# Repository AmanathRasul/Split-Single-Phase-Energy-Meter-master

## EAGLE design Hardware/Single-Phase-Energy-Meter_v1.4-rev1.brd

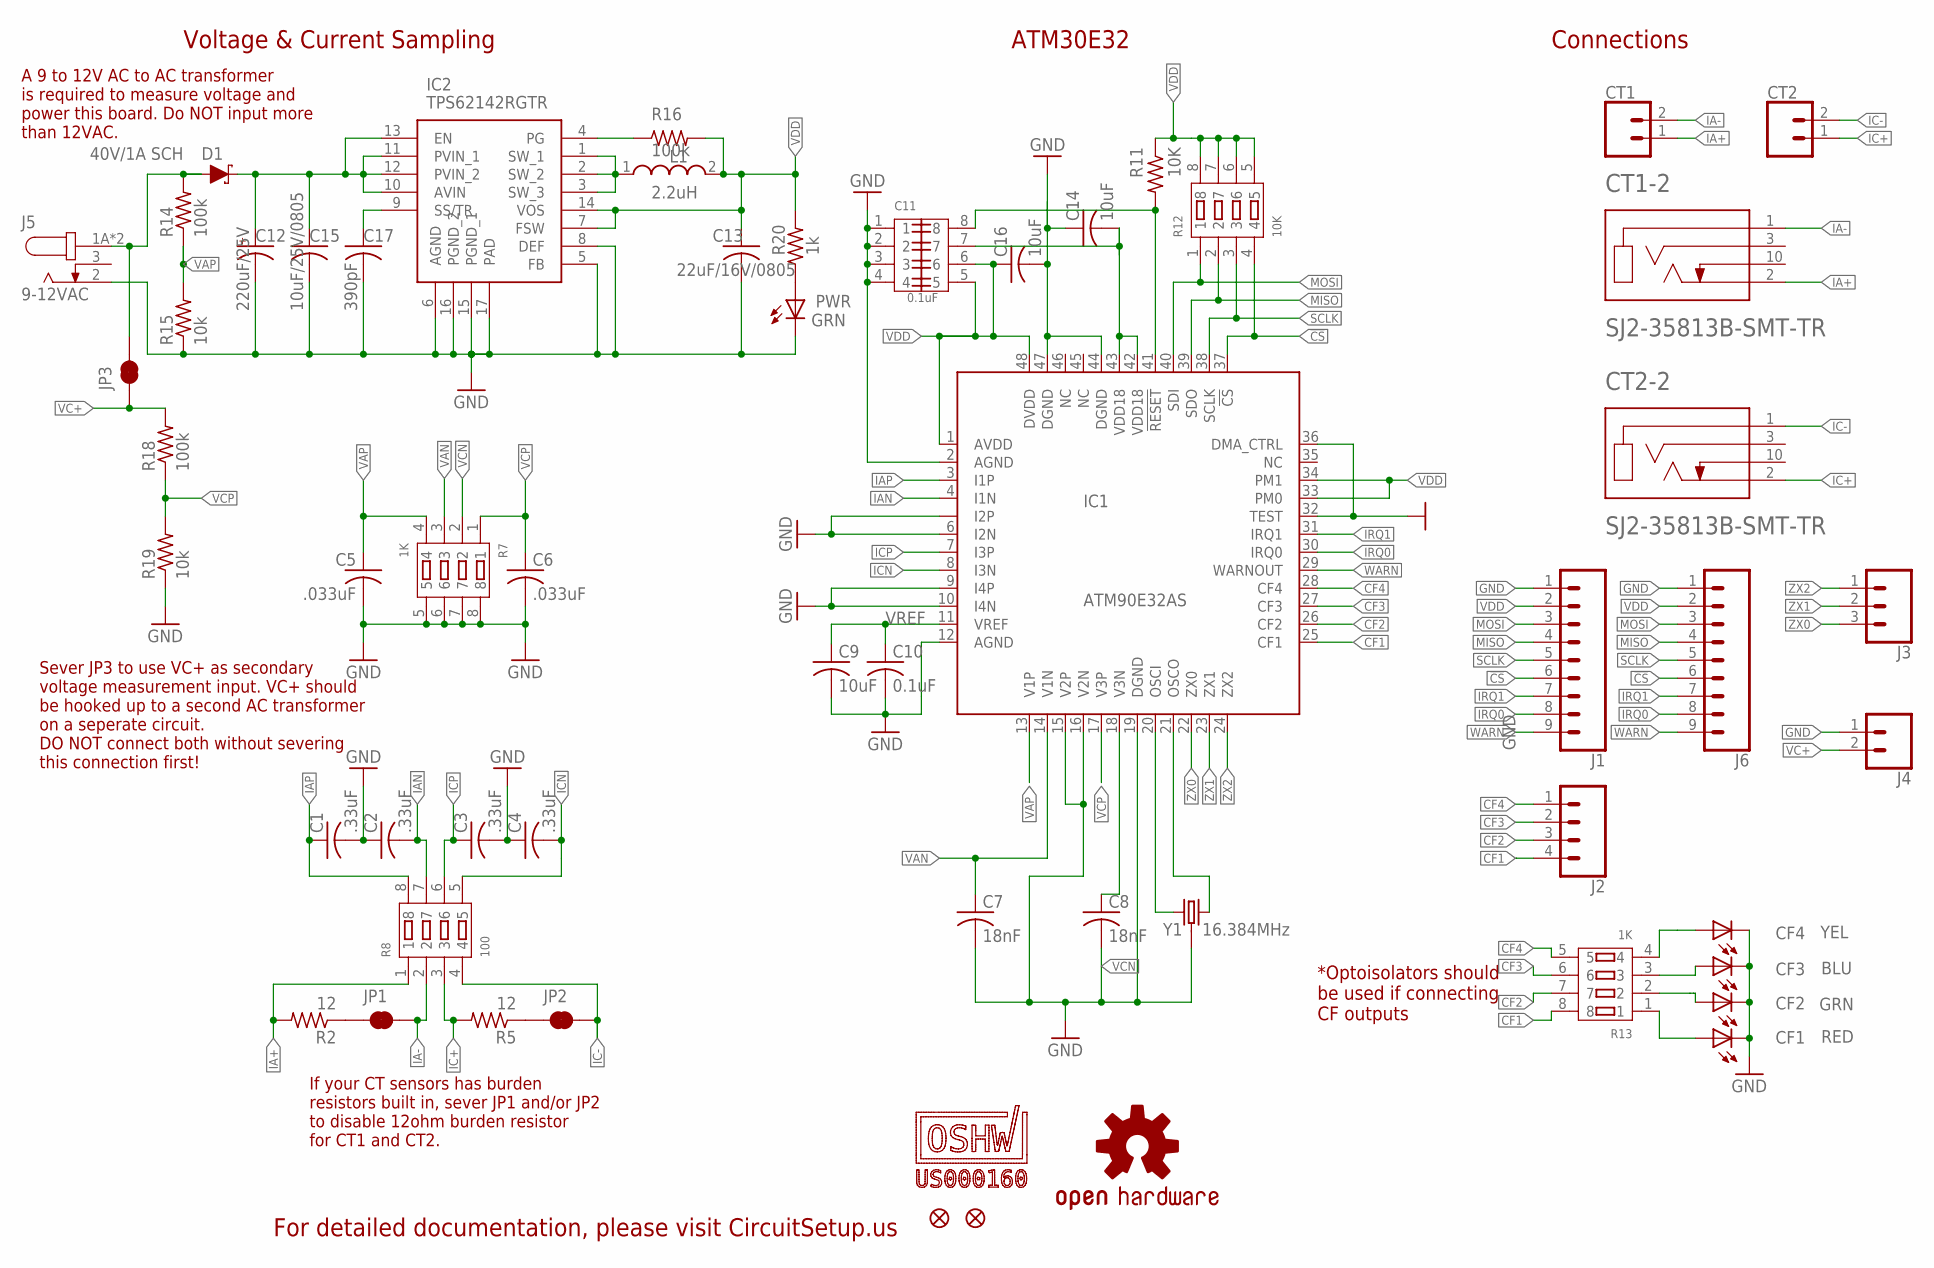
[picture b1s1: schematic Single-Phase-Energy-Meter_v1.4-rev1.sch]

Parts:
C1, C2, C3, C4: .33uF; C0603
C5, C6: .033uF; C0603
C7, C8: 18nF; C0603
C9, C14, C16: 10uF; C0603
C10: 0.1uF; C0603
C11: 0.1uF; CAPCAF80P320X160X70-8
C12: 220uF/25V; 153CLV-0605
C13: 22uF/16V/0805; C0805
C15: 10uF/25V/0805; C0805
C17: 390pF; C0603
CF1: RED; CHIP-LED0603
CF2: GRN; CHIP-LED0603
CF3: BLU; CHIP-LED0603
CF4: YEL; CHIP-LED0603
CT1, CT2: CONN_023.5MM; SCREWTERMINAL-3.5MM-2
CT1-2, CT2-2: SJ2-35813B-SMT-TR; CUI_SJ2-35813B-SMT-TR
D1: 40V/1A SCH; SMA-DIODE
FD1, FD2: FIDUCIALUFIDUCIAL; FIDUCIAL-MICRO
IC1: ATM90E32AS; QFP50P900X900X120-48N
IC2: TPS62142RGTR; QFN50P300X300X100-17N
J1, J6: CONN_09; 1X09
J2: CONN_04; 1X04
J3: CONN_03; 1X03
J4: CONN_02; 1X02
J5: 9-12VAC; CUI_PJ-002AH-SMT-TR
JP1, JP2, JP3: JUMPER-SMT_2_NC_TRACE_SILK; SMT-JUMPER_2_NC_TRACE_SILK
L1: 2.2uH; INDPM4042X200N
LOGO1: OSHW-LOGOS; OSHW-LOGO-S
PWR: GRN; CHIP-LED0603
R2, R5: 12; R0603
R7, R13: 1K; RA1206-8
R8: 100; RA1206-8
R11: 10K; R0603
R12: 10K; RA1206-8
R14, R16, R18: 100k; R0603
R15, R19: 10k; R0603
R20: 1k; R0603
U$1: CS_OSHW_LOGOS; OSHW160
Y1: 16.384MHz; CRYSTAL-SMD-3.2X2.5MM

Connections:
!CS: IC1.37 (!CS), J1.6, J6.6, R12.4
!RESET: C11.8, IC1.41 (!RESET), R11.2
CF1: IC1.25 (CF1), J2.4, R13.8
CF2: IC1.26 (CF2), J2.3, R13.7
CF3: IC1.27 (CF3), J2.2, R13.6
CF4: IC1.28 (CF4), J2.1, R13.5
GND: C1.2, C2.1, C3.2, C4.1, C5.2, C6.2, C7.2, C8.2, C9.2, C10.2, C11.1, C11.2, C11.3, C11.4, C12.-, C13.2, C14.1, C15.2, C16.2, C17.2, CF1.C, CF2.C, CF3.C, CF4.C, IC1.2 (AGND), IC1.5 (I2P), IC1.6 (I2N), IC1.9 (I4P), IC1.10 (I4N), IC1.12 (AGND), IC1.15 (V2P), IC1.16 (V2N), IC1.19 (DGND), IC1.32 (TEST), IC1.36 (DMA_CTRL), IC1.44 (DGND), IC1.47 (DGND), IC2.5 (FB), IC2.6 (AGND), IC2.8 (DEF), IC2.15 (PGND_1), IC2.16 (PGND_2), IC2.17 (PAD), J1.1, J4.1, J5.2, J6.1, PWR.C, R7.5, R7.6, R7.7, R7.8, R15.1, R19.1, Y1.2 (3), Y1.4 (3)
IA+: CT1.1, CT1-2.2 (TIP), R2.2, R8.1
IA-: CT1.2, CT1-2.1 (SLEEVE), JP1.2, R8.2
IAN: C2.2, IC1.4 (I1N), R8.7
IAP: C1.1, IC1.3 (I1P), R8.8
IC+: CT2.1, CT2-2.2 (TIP), R5.2, R8.3
IC-: CT2.2, CT2-2.1 (SLEEVE), JP2.2, R8.4
ICN: C4.2, IC1.8 (I3N), R8.5
ICP: C3.1, IC1.7 (I3P), R8.6
IRQ0: IC1.30 (IRQ0), J1.8, J6.8
IRQ1: IC1.31 (IRQ1), J1.7, J6.7
MISO: IC1.39 (SDO), J1.4, J6.4, R12.2
MOSI: IC1.40 (SDI), J1.3, J6.3, R12.1
unnamed: JP1.1, R2.1
unnamed: JP2.1, R5.1
unnamed: CF4.A, R13.4
unnamed: CF3.A, R13.3
unnamed: CF2.A, R13.2
unnamed: CF1.A, R13.1
unnamed: PWR.A, R20.1
OSCI: IC1.20 (OSCI), Y1.1
OSCO: IC1.21 (OSCO), Y1.3 (2)
PG: IC2.4 (PG), R16.1
SCLK: IC1.38 (SCLK), J1.5, J6.5, R12.3
SS/TR: C17.1, IC2.9 (SS/TR)
SW: IC2.1 (SW_1), IC2.2 (SW_2), IC2.3 (SW_3), L1.1
VA+: D1.A, J5.1A (1), J5.1B (1), JP3.2, R14.2
VAN: C7.1, IC1.14 (V1N), R7.3
VAP: C5.1, IC1.13 (V1P), R7.4, R14.1, R15.2
VC+: J4.2, JP3.1, R18.2
VCN: C8.1, IC1.18 (V3N), R7.2
VCP: C6.1, IC1.17 (V3P), R7.1, R18.1, R19.2
VDD: C11.5, C11.6, C13.1, C16.1, IC1.1 (AVDD), IC1.33 (PM0), IC1.34 (PM1), IC1.48 (DVDD), IC2.7 (FSW), IC2.14 (VOS), J1.2, J6.2, L1.2, R11.1, R12.5, R12.6, R12.7, R12.8, R16.2, R20.2
VDD18: C11.7, C14.2, IC1.42 (VDD18), IC1.43 (VDD18)
VIN1: C12.+, C15.1, D1.C, IC2.10 (AVIN), IC2.11 (PVIN_1), IC2.12 (PVIN_2), IC2.13 (EN)
VREF: C9.1, C10.1, IC1.11 (VREF)
WARN: IC1.29 (WARNOUT), J1.9, J6.9
ZX0: IC1.22 (ZX0), J3.3
ZX1: IC1.23 (ZX1), J3.2
ZX2: IC1.24 (ZX2), J3.1

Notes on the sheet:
ATM30E32
Voltage & Current Sampling
Connections
*Optoisolators should be used if connecting CF outputs
If your CT sensors has burden resistors built in, sever JP1 and/or JP2 to disable 12ohm burden resistor for CT1 and CT2.
Sever JP3 to use VC+ as secondary voltage measurement input. VC+ should be hooked up to a second AC transformer on a seperate circuit. DO NOT connect both without severing this connection first!
A 9 to 12V AC to AC transformer is required to measure voltage and power this board. Do NOT input more than 12VAC.
For detailed documentation, please visit CircuitSetup.us

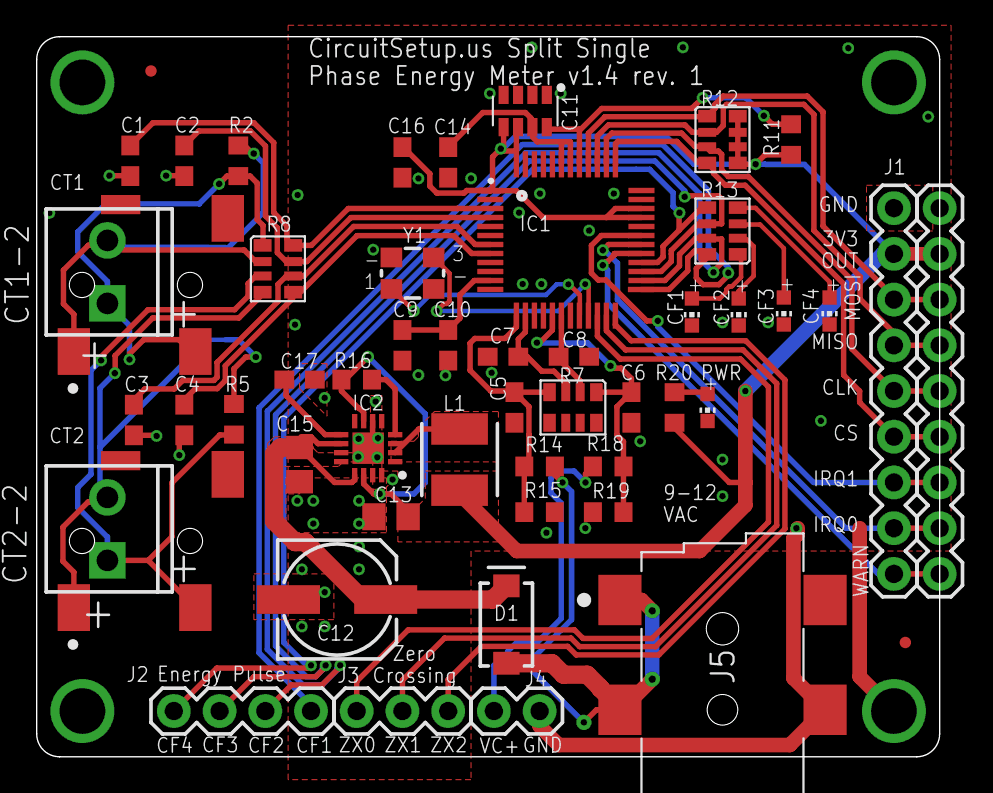
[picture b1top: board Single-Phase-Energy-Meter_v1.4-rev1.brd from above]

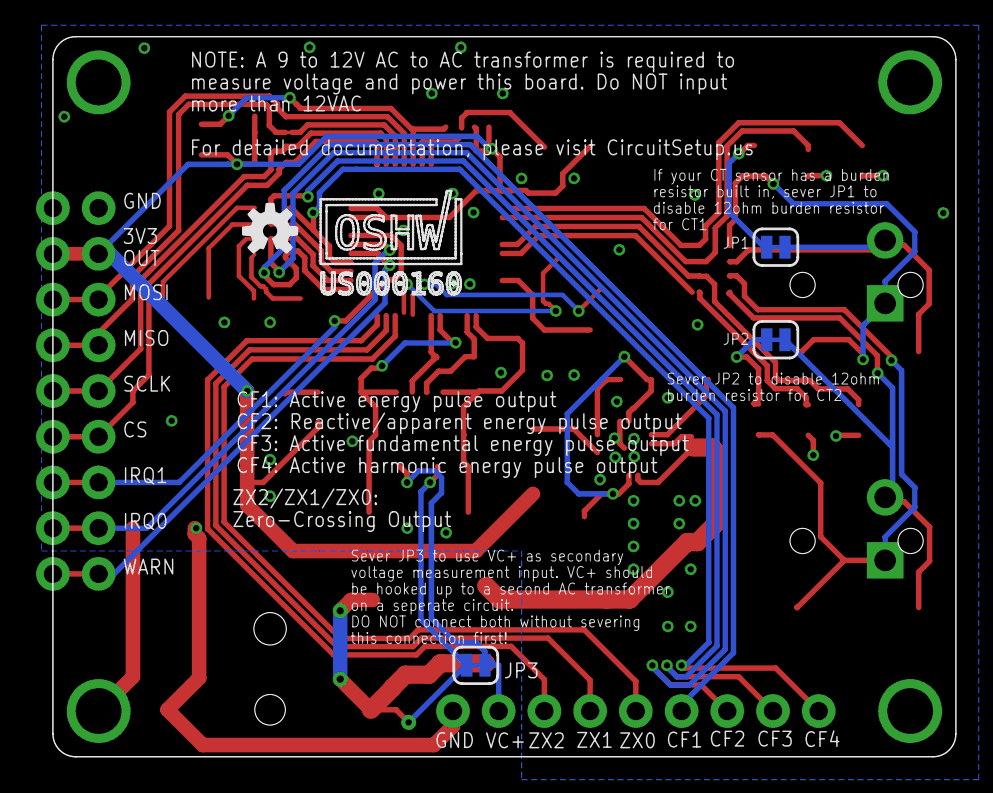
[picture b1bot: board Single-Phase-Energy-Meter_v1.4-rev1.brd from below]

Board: 2 copper layers, 50.2 x 40.0 mm, 57 parts (5 on the bottom side), 46 nets.

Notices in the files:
parts and their libraries:
SparkFun-Connectors: Licensing: Creative Commons ShareAlike 4.0 International - https://creativecommons.org/licenses/by-sa/4.0
